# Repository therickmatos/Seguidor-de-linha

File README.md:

# Seguidor de linha — baseado no EVA-RT

Robotracer com ventoinha centrífuga para uma competição baseada no regulamento do TRIF 7ª edição.
Baseado no [EVA-RT](https://github.com/EXOTIC-TEAM-MX/EVA-RT) (© EXOTIC TEAM MX, AGPL-3.0).

- ATmega328P-AU, firmware EVA-RT 1.2.2 (mesmo mapa de pinos)
- 2× DRV8874 (motores coreless 1020), AO3400A na ventoinha
- Barra de 12× QRE1113 + 74HC4067, sensores de marca nos braços laterais
- LiPo 2S 350 mAh, contorno "B degraus" de 148,2 × 57,6 mm

## Estado
- [x] Componentes definidos
- [x] Contorno definitivo (`hardware/contorno/`)
- [x] Esquemático rev 1.0 em KiCad (`hardware/seguidor_base/seguidor_base.pdf`; fonte em `ferramentas/esquematico/`)
- [ ] Importação no EasyEDA Pro (em andamento; conferir com `hardware/seguidor_base/REDES.md`)
- [ ] Layout da placa (EasyEDA Pro)
- [ ] Pedido na JLC
- [ ] Montagem e firmware

## Estrutura
| Pasta | Conteúdo |
|---|---|
| `docs/` | decisões (as mais novas: `DECISOES_2026-11-04.md`), contorno e esquemático |
| `hardware/contorno/` | contorno B definitivo (DXF) e figuras de conferência |
| `hardware/seguidor_base/` | esquemático rev 1.0 (projeto KiCad, PDF), BOM, lista de redes (`REDES.md`) |
| `hardware/barra_v1/` | Gerber da barra de sensores V1 (12 sensores) |
| `hardware/figuras/` | posição do conector do Bluetooth |
| `Perseguidor de linha/` | perseguidor (placa sem os braços + receptor IR KY-022): projeto EasyEDA Pro e revisão |
| `ferramentas/esquematico/` | scripts que geram o esquemático KiCad, a BOM e a lista de redes |
| `referencias/eva-rt/` | cópia do EVA-RT: projeto EasyEDA Pro, Gerbers, PDFs, STL e firmware |

O seguidor em fenolite é outro projeto e não está neste repositório.

## Licença
GNU Affero General Public License v3.0 (`LICENSE`), a mesma do EVA-RT.

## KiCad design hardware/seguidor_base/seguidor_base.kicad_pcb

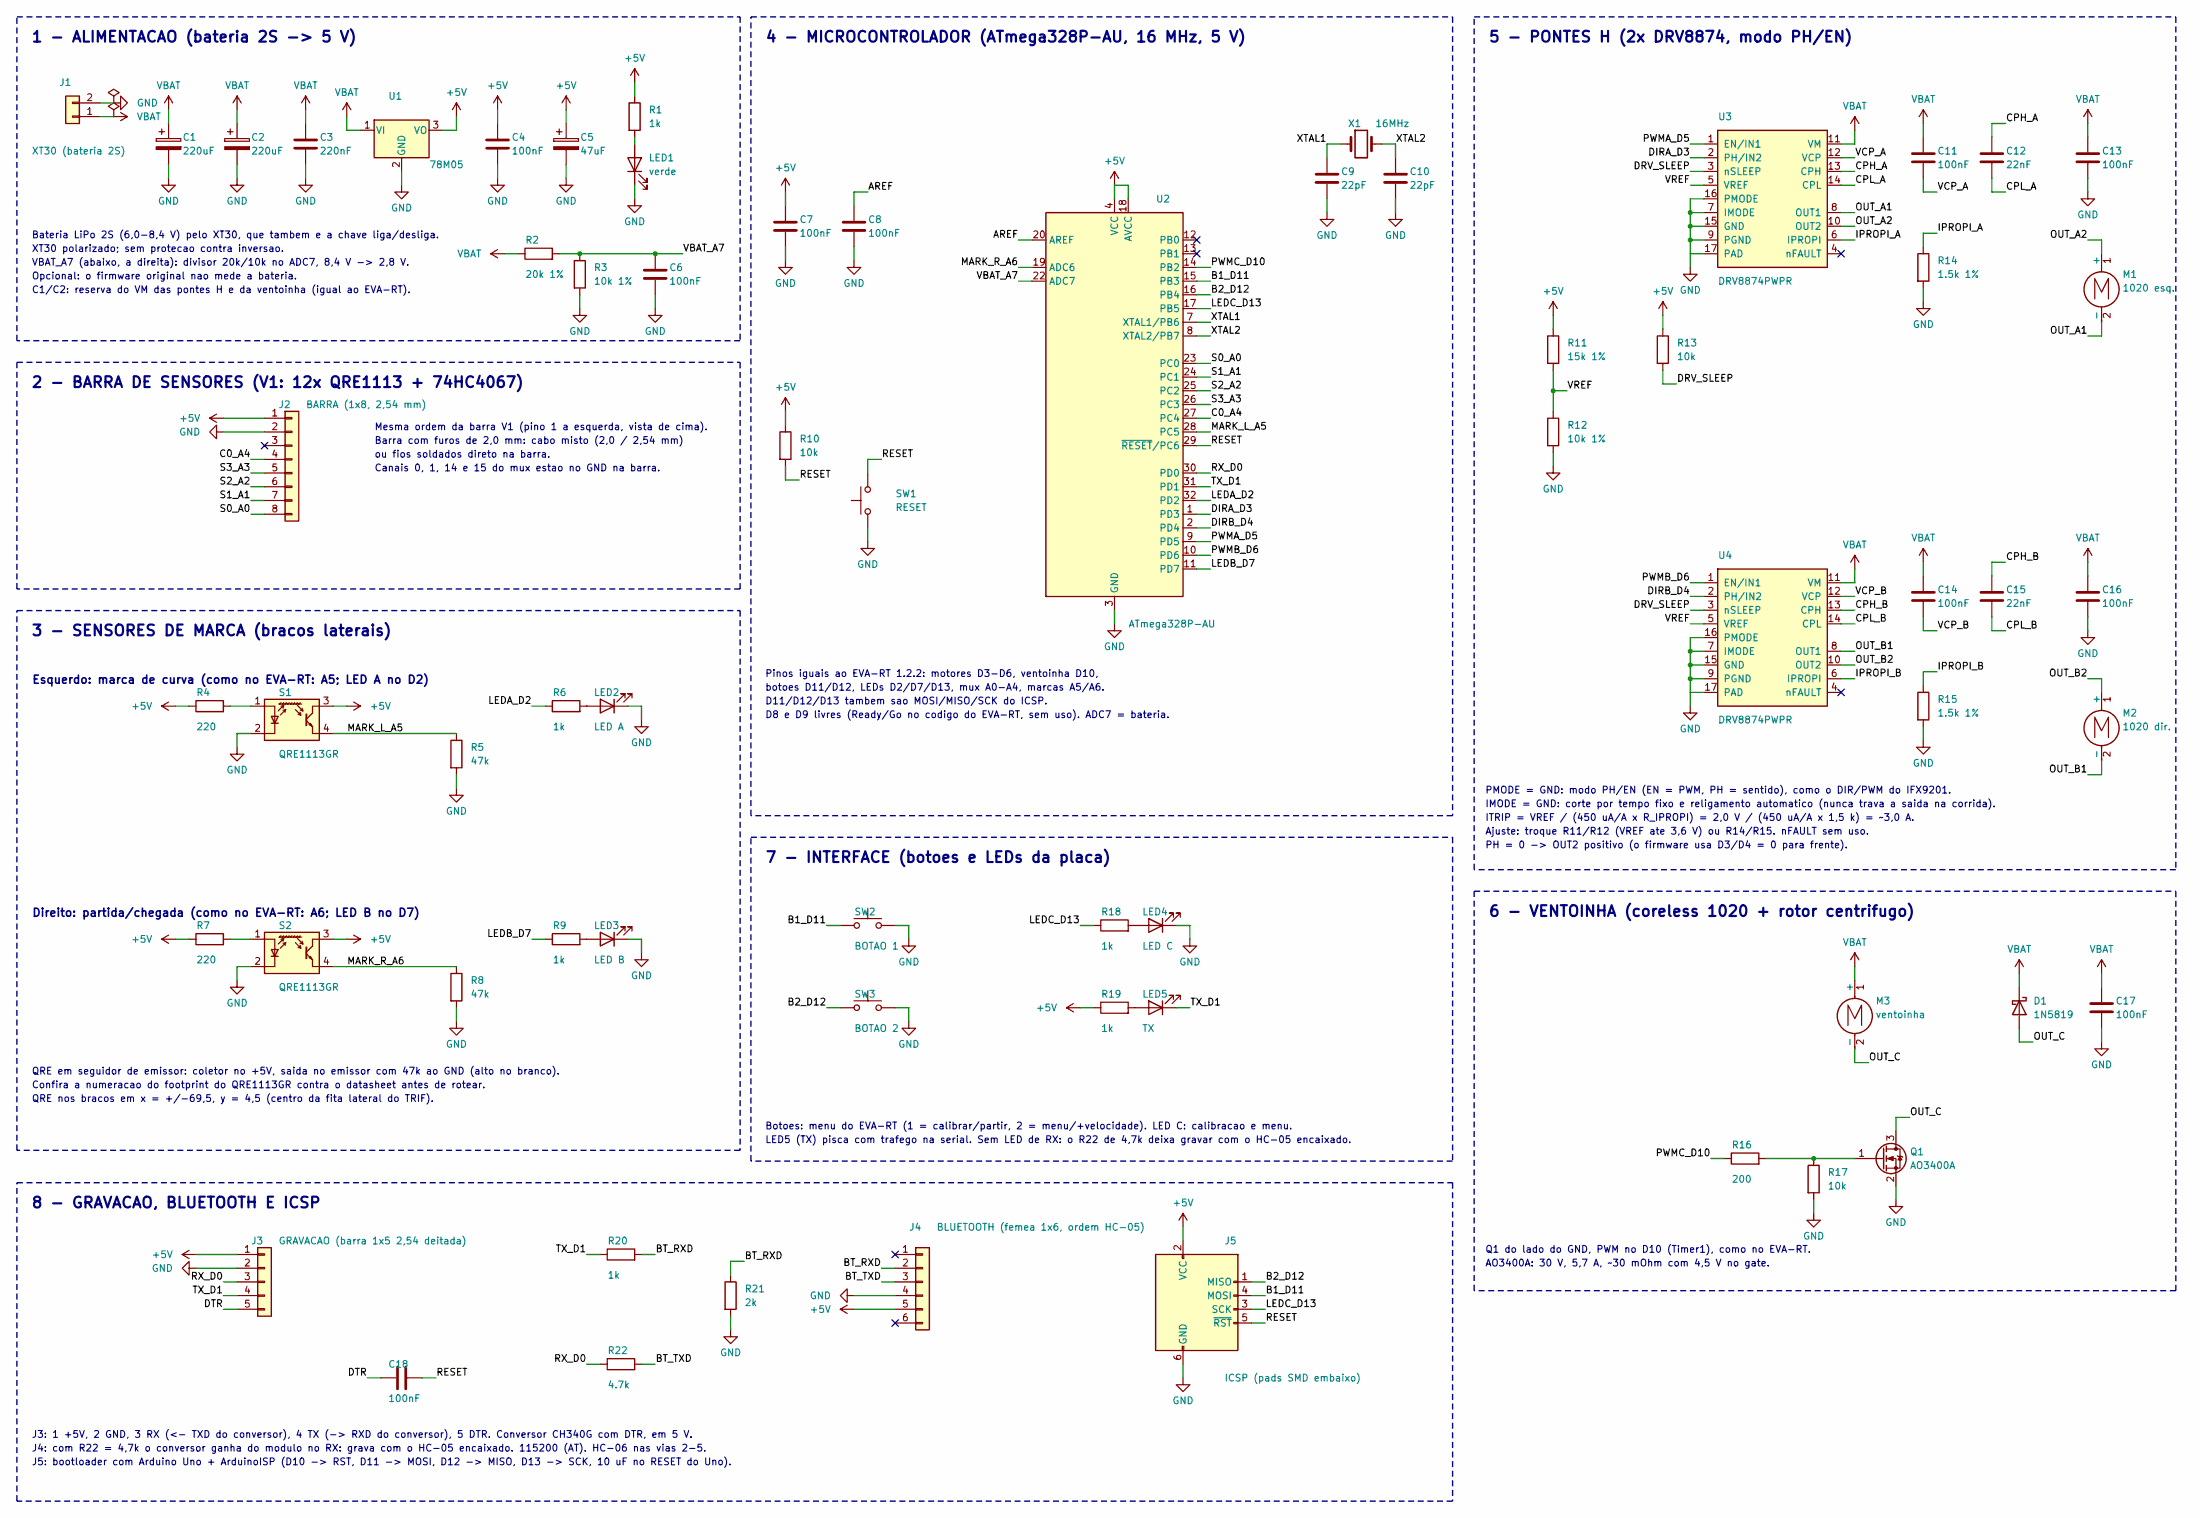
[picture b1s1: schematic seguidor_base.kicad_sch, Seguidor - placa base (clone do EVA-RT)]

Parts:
C1, C2: 220uF; C_RAD_D6.3_P2.5
C3: 220nF; C0603
C4, C6, C7, C8, C11, C13, C14, C16, C17, C18: 100nF; C0603
C5: 47uF; C1210
C9, C10: 22pF; C0603
C12, C15: 22nF; C0603
D1: 1N5819; SOD123
J1: XT30 (bateria 2S); XT30_VERTICAL_M_PROPOSTA; LCSC C99101
J2: BARRA (1x8, 2,54 mm); HDR_1x08_P2.54
J3: GRAVACAO (barra 1x5 2,54 deitada); HDR_1x05_P2.54_SMD_DEITADA
J4: BLUETOOTH (femea 1x6, ordem HC-05); HDR_F_1x06_P2.54
J5: ICSP (pads SMD embaixo); ICSP_6P_SMD_BOT
LED1: verde; LED0603
LED2: LED A; LED0603
LED3: LED B; LED0603
LED4: LED C; LED0603
LED5: TX; LED0603
M1: 1020 esq.; MOTOR_1020_2P
M2: 1020 dir.; MOTOR_1020_2P
M3: ventoinha; MOTOR_1020_2P
Q1: AO3400A; SOT23_AO3400A; LCSC C20917
R1, R6, R9, R18, R19, R20: 1k; R0603
R2: 20k 1%; R0603
R3, R12: 10k 1%; R0603
R4, R7: 220; R0603
R5, R8: 47k; R0603
R10, R13, R17: 10k; R0603
R11: 15k 1%; R0603
R14, R15: 1.5k 1%; R0603
R16: 200; R0603
R21: 2k; R0603
R22: 4.7k; R0603
S1, S2: QRE1113GR; QRE1113GR_SMD
SW1: RESET; SW_TACT_3x6_SMD_2P_RESET; LCSC C19271064
SW2: BOTAO 1; SW_TACT_3x6_SMD_2P; LCSC C19271064
SW3: BOTAO 2; SW_TACT_3x6_SMD_2P; LCSC C19271064
U1: 78M05; DPAK_TO252_3; LCSC C111265
U2: ATmega328P-AU; TQFP32_7x7_P0.8; LCSC C14877
U3, U4: DRV8874PWPR; HTSSOP16_PWP_DRV8874; LCSC C1855818
X1: 16MHz; XTAL_TXC_7A_5032_2P; LCSC C2450102

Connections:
+5V: C4.1, C5.1, C7.1, J2.1, J3.1, J4.5, J5.2 (VCC), R1.1, R4.1, R7.1, R10.1, R11.1, R13.1, R19.1, S1.3, S2.3, U1.3 (VO), U2.4 (VCC), U2.6 (VCC), U2.18 (AVCC)
AREF: C8.1, U2.20 (AREF)
B1_D11: J5.4 (MOSI), SW2.1, U2.15 (PB3)
B2_D12: J5.1 (MISO), SW3.1, U2.16 (PB4)
BT_RXD: J4.2, R20.2, R21.1
BT_TXD: J4.3, R22.2
C0_A4: J2.4, U2.27 (PC4)
CPH_A: C12.1, U3.13 (CPH)
CPH_B: C15.1, U4.13 (CPH)
CPL_A: C12.2, U3.14 (CPL)
CPL_B: C15.2, U4.14 (CPL)
DIRA_D3: U2.1 (PD3), U3.2 (PH/IN2)
DIRB_D4: U2.2 (PD4), U4.2 (PH/IN2)
DRV_SLEEP: R13.2, U3.3 (nSLEEP), U4.3 (nSLEEP)
DTR: C18.1, J3.5
GND: C1.2, C2.2, C3.2, C4.2, C5.2, C6.2, C7.2, C8.2, C9.2, C10.2, C13.2, C16.2, C17.2, J1.2, J2.2, J3.2, J4.4, J5.6 (GND), LED1.1 (K), LED2.1 (K), LED3.1 (K), LED4.1 (K), Q1.2 (S), R3.2, R5.2, R8.2, R12.2, R14.2, R15.2, R17.2, R21.2, S1.2 (K), S2.2 (K), SW1.1, SW2.2, SW3.2, U1.2 (GND), U2.3 (GND), U2.5 (GND), U2.21 (GND), U3.7 (IMODE), U3.9 (PGND), U3.15 (GND), U3.16 (PMODE), U3.17 (PAD), U4.7 (IMODE), U4.9 (PGND), U4.15 (GND), U4.16 (PMODE), U4.17 (PAD)
IPROPI_A: R14.1, U3.6 (IPROPI)
IPROPI_B: R15.1, U4.6 (IPROPI)
LEDA_D2: R6.1, U2.32 (PD2)
LEDB_D7: R9.1, U2.11 (PD7)
LEDC_D13: J5.3 (SCK), R18.1, U2.17 (PB5)
MARK_L_A5: R5.1, S1.4, U2.28 (PC5)
MARK_R_A6: R8.1, S2.4, U2.19 (ADC6)
unnamed: LED1.2 (A), R1.2
unnamed: LED2.2 (A), R6.2
unnamed: LED3.2 (A), R9.2
unnamed: LED4.2 (A), R18.2
unnamed: LED5.2 (A), R19.2
unnamed: Q1.1 (G), R16.2, R17.1
unnamed: R4.2, S1.1 (A)
unnamed: R7.2, S2.1 (A)
OUT_A1: M1.2 (-), U3.8 (OUT1)
OUT_A2: M1.1 (+), U3.10 (OUT2)
OUT_B1: M2.2 (-), U4.8 (OUT1)
OUT_B2: M2.1 (+), U4.10 (OUT2)
OUT_C: D1.2 (A), M3.2 (-), Q1.3 (D)
PWMA_D5: U2.9 (PD5), U3.1 (EN/IN1)
PWMB_D6: U2.10 (PD6), U4.1 (EN/IN1)
PWMC_D10: R16.1, U2.14 (PB2)
RESET: C18.2, J5.5 (~RST), R10.2, SW1.2, U2.29 (~RESET/PC6)
RX_D0: J3.3, R22.1, U2.30 (PD0)
S0_A0: J2.8, U2.23 (PC0)
S1_A1: J2.7, U2.24 (PC1)
S2_A2: J2.6, U2.25 (PC2)
S3_A3: J2.5, U2.26 (PC3)
TX_D1: J3.4, LED5.1 (K), R20.1, U2.31 (PD1)
VBAT: C1.1, C2.1, C3.1, C11.1, C13.1, C14.1, C16.1, C17.1, D1.1 (K), J1.1, M3.1 (+), R2.1, U1.1 (VI), U3.11 (VM), U4.11 (VM)
VBAT_A7: C6.1, R2.2, R3.1, U2.22 (ADC7)
VCP_A: C11.2, U3.12 (VCP)
VCP_B: C14.2, U4.12 (VCP)
VREF: R11.2, R12.1, U3.5 (VREF), U4.5 (VREF)
XTAL1: C9.1, U2.7 (XTAL1/PB6), X1.1
XTAL2: C10.1, U2.8 (XTAL2/PB7), X1.2

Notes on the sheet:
1 - ALIMENTACAO (bateria 2S -> 5 V)
Bateria LiPo 2S (6,0-8,4 V) pelo XT30, que tambem e a chave liga/desliga.
XT30 polarizado; sem protecao contra inversao.
VBAT_A7 (abaixo, a direita): divisor 20k/10k no ADC7, 8,4 V -> 2,8 V.
Opcional: o firmware original nao mede a bateria.
C1/C2: reserva do VM das pontes H e da ventoinha (igual ao EVA-RT).
2 - BARRA DE SENSORES (V1: 12x QRE1113 + 74HC4067)
Mesma ordem da barra V1 (pino 1 a esquerda, vista de cima).
Barra com furos de 2,0 mm: cabo misto (2,0 / 2,54 mm)
ou fios soldados direto na barra.
Canais 0, 1, 14 e 15 do mux estao no GND na barra.
3 - SENSORES DE MARCA (bracos laterais)
Esquerdo: marca de curva (como no EVA-RT: A5; LED A no D2)
Direito: partida/chegada (como no EVA-RT: A6; LED B no D7)
QRE em seguidor de emissor: coletor no +5V, saida no emissor com 47k ao GND (alto no branco).
Confira a numeracao do footprint do QRE1113GR contra o datasheet antes de rotear.
QRE nos bracos em x = +/-69,5, y = 4,5 (centro da fita lateral do TRIF).
4 - MICROCONTROLADOR (ATmega328P-AU, 16 MHz, 5 V)
Pinos iguais ao EVA-RT 1.2.2: motores D3-D6, ventoinha D10,
botoes D11/D12, LEDs D2/D7/D13, mux A0-A4, marcas A5/A6.
D11/D12/D13 tambem sao MOSI/MISO/SCK do ICSP.
D8 e D9 livres (Ready/Go no codigo do EVA-RT, sem uso). ADC7 = bateria.
5 - PONTES H (2x DRV8874, modo PH/EN)
PMODE = GND: modo PH/EN (EN = PWM, PH = sentido), como o DIR/PWM do IFX9201.
IMODE = GND: corte por tempo fixo e religamento automatico (nunca trava a saida na corrida).
ITRIP = VREF / (450 uA/A x R_IPROPI) = 2,0 V / (450 uA/A x 1,5 k) = ~3,0 A.
Ajuste: troque R11/R12 (VREF ate 3,6 V) ou R14/R15. nFAULT sem uso.
PH = 0 -> OUT2 positivo (o firmware usa D3/D4 = 0 para frente).
6 - VENTOINHA (coreless 1020 + rotor centrifugo)
Q1 do lado do GND, PWM no D10 (Timer1), como no EVA-RT.
AO3400A: 30 V, 5,7 A, ~30 mOhm com 4,5 V no gate.
7 - INTERFACE (botoes e LEDs da placa)
Botoes: menu do EVA-RT (1 = calibrar/partir, 2 = menu/+velocidade). LED C: calibracao e menu.
LED5 (TX) pisca com trafego na serial. Sem LED de RX: o R22 de 4,7k deixa gravar com o HC-05 encaixado.
8 - GRAVACAO, BLUETOOTH E ICSP
J3: 1 +5V, 2 GND, 3 RX (<- TXD do conversor), 4 TX (-> RXD do conversor), 5 DTR. Conversor CH340G com DTR, em 5 V.
J4: com R22 = 4,7k o conversor ganha do modulo no RX: grava com o HC-05 encaixado. 115200 (AT). HC-06 nas vias 2-5.
J5: bootloader com Arduino Uno + ArduinoISP (D10 -> RST, D11 -> MOSI, D12 -> MISO, D13 -> SCK, 10 uF no RESET do Uno).

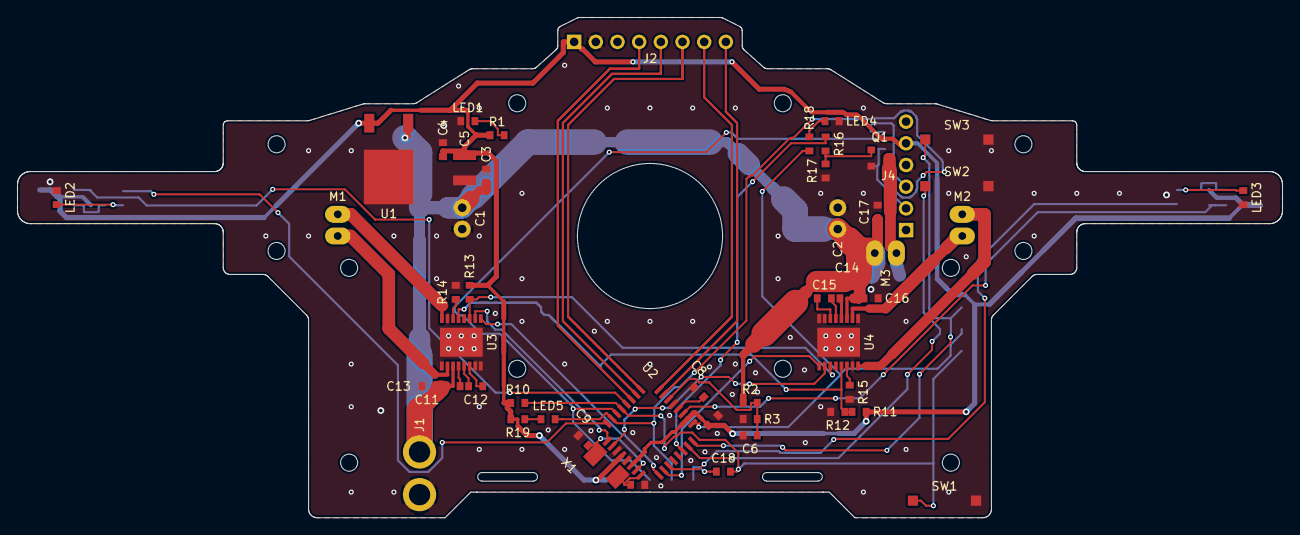
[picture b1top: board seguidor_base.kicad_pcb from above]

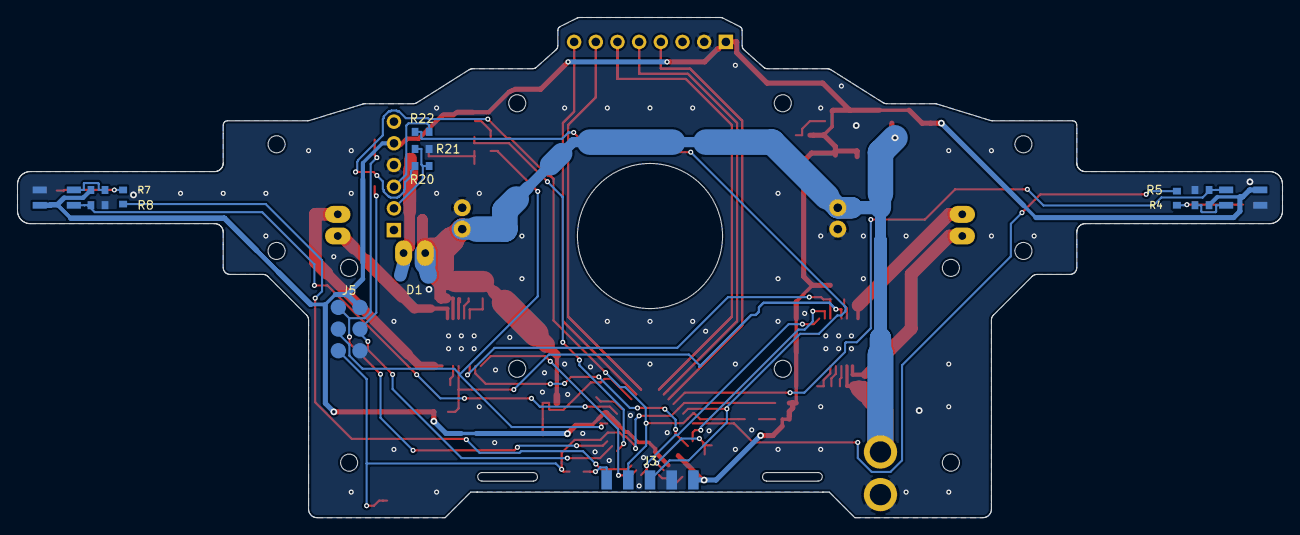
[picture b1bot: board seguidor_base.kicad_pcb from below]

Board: 2 copper layers, 148.2 x 58.6 mm, 65 parts (14 on the bottom side), 53 nets.

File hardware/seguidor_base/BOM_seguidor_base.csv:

Qtd;Referencias;Valor;Encapsulamento;LCSC;Montagem;EVA-RT;Observacao
2;C1 C2;220uF;eletrolitico 25 V, radial D6,3 mm P2,5;;sim;igual;entre os pes da carcaca, como no EVA-RT
1;C3;220nF;0603 50 V;;sim;igual;
4;C4 C7 C8 C18;100nF;0603;;sim;"igual; novo";"junto aos pinos VCC; AREF (referencia = AVCC no firmware); reset automatico pelo DTR"
1;C5;47uF;ceramico X5R >= 10 V, 1210;;sim;igual;"07/11: 1210 (achado pelo Erick); o tantalo 3216 do EVA-RT tambem serve com footprint 3216"
2;C9 C10;22pF;0603;;sim;novo;
2;C11 C14;100nF;0603 16 V X7R;;sim;novo;VCP -> VM
2;C12 C15;22nF;0603 50 V X7R;;sim;novo;CPH -> CPL (tensao >= VM)
2;C13 C16;100nF;0603 25 V X7R;;sim;igual;VM, junto ao pino 11
1;C17;100nF;0603 25 V;;sim;igual;
1;D1;1N5819;SOD-123 (B5819W) ou 1N5819 nos terminais do motor;;sim;novo;"diodo de roda livre (novo; o EVA-RT nao tem)"
1;J1;XT30 (bateria 2S);"XT30U-M (macho de cabo; copos soldados nos furos, em pe)";C99101;sim;VIN;"pino 1 = + (lado reto), pino 2 = -; em pe por dentro do suporte esq.; medir os copos e cortar rente embaixo; versao de placa: XT30UPB-M (C428721)"
1;J2;BARRA (1x8, 2,54 mm);barra de pinos 1x8 2,54 mm;;sim;FPC1 (FPC 10 vias);
1;J3;GRAVACAO (barra 1x5 2,54 deitada);5 pads SMD 1,25 x 2,25 + barra macho 1x5 2,54 deitada;;sim;Converter Conn Master;borda traseira, face de baixo (como o EVA-RT)
1;J4;BLUETOOTH (femea 1x6, ordem HC-05);barra femea 1x6 2,54 mm;;sim;novo;"frente direita, x = 32,5; HC-06 nas vias 2-5 (virado)"
1;J5;ICSP (pads SMD embaixo);6 pads SMD D1,8 em grade 2,54;;sim;USB to ASP Conn Master;"posicoes do EVA-RT: x 33,97/36,51; y -8,36/-10,90/-13,44"
1;LED1;verde;0603;;sim;igual;indica 5 V presente
1;LED2;LED A;0603;;sim;igual;
1;LED3;LED B;0603;;sim;igual;
1;LED4;LED C;0603;;sim;igual;"vermelho; o LED em paralelo do EVA-RT foi retirado"
1;LED5;TX;0603;;sim;igual;
1;M1;1020 esq.;2 pads;;sim;igual;"coreless 1020 7,4 V; se girar ao contrario, inverta os fios"
1;M2;1020 dir.;2 pads;;sim;igual;"coreless 1020 7,4 V; se girar ao contrario, inverta os fios"
1;M3;ventoinha;2 pads;;sim;igual;coreless 1020 7,4 V
1;Q1;AO3400A;SOT-23 (1 = G, 2 = S, 3 = D);C20917;sim;Q1 (outro MOSFET);"no lugar do IRFR3411/RM10N100LD; liga totalmente com 5 V no gate"
6;R1 R6 R9 R18 R19 R20;1k;0603;;sim;"igual; novo";divisor 5 V -> 3,3 V
2;R4 R7;220;0603;;sim;igual;
2;R5 R8;47k;0603;;sim;igual;
3;R10 R13 R17;10k;0603;;sim;"R3 (1k); novo; igual";"EVA-RT usava 1k; 10k com reset automatico por DTR; nSLEEP sempre alto (pull-down interno de 100k); gate -> GND (desligado no boot)"
1;R11;15k 1%;0603;;sim;novo;VREF = 2,0 V
1;R12;10k 1%;0603;;sim;novo;VREF = 2,0 V
2;R14 R15;1.5k 1%;0603;;sim;novo;IPROPI -> limite de corrente
1;R16;200;0603;;sim;igual;gate
1;R21;2k;0603;;sim;novo;divisor 5 V -> 3,3 V
1;R22;4.7k;0603;;sim;novo;4,7k: grava com o HC-05 encaixado (sem LED de RX)
2;S1 S2;QRE1113GR;SMD 4 pinos;;sim;igual;datasheet: 1 = anodo, 2 = catodo, 3 = coletor, 4 = emissor
1;SW1;RESET;chave tactil SMD 3,7 x 6,1, 2 terminais (Jianfu TVBM17-025CF-R);C19271064;sim;igual;"terminais com 8,0 de ponta a ponta; pads encurtados (8,6 no total) para caber ao lado do J4"
1;SW2;BOTAO 1;chave tactil SMD 3,7 x 6,1, 2 terminais (Jianfu TVBM17-025CF-R);C19271064;sim;igual;"terminais com 8,0 de ponta a ponta; pads encurtados (8,6 no total) para caber ao lado do J4"
1;SW3;BOTAO 2;chave tactil SMD 3,7 x 6,1, 2 terminais (Jianfu TVBM17-025CF-R);C19271064;sim;igual;"terminais com 8,0 de ponta a ponta; pads encurtados (8,6 no total) para caber ao lado do J4"
1;U1;78M05;TO-252 (DPAK);C111265;sim;igual;
1;U2;ATmega328P-AU;TQFP-32;C14877;sim;igual;do Nano/Uno doador (com bootloader) ou novo + bootloader pelo ICSP
2;U3 U4;DRV8874PWPR;HTSSOP-16 (PWP), pad termico com vias;C1855818;sim;"IFX_A1 (IFX9201); IFX_B1 (IFX9201)";"esq.; dir."
1;X1;16MHz;cristal SMD 5032 de 2 pads (TXC 7A-16.000MAAJ-T);C2450102;sim;X1 (ressonador 3 pinos);16 MHz, CL 18 pF, ESR 50 ohm, +-30 ppm, 1,2 mm de altura (fica sob a bateria)
1;C6;100nF;0603;;opcional (bateria);novo;filtro da medicao (opcional)
1;R2;20k 1%;0603;;opcional (bateria);novo;medicao da bateria (opcional)
1;R3;10k 1%;0603;;opcional (bateria);novo;medicao da bateria (opcional)

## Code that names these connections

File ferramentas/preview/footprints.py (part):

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    [_pad("1", -4.25, 0, 4.5, 2.0), _pad("2", 4.25, 0, 4.5, 2.0)],
    (11.4, 4.7), 3.5, False,
    "Cristal HC-49/S SMD 2 terminais (X1 16 MHz, alternativa do BOM). KiCad "
    "Crystal_SMD_HC49-SD: pads 4,5 x 2,0 em +-4,25; corpo 11,4 x 4,7 (F.Fab). Pino 1 = XTAL1, "
    "pino 2 = XTAL2 (sem pinos de GND). Altura 3,5 estimada. Default de X1: por ser o maior, "
    "serve de caso conservador para colisao.")

# 07/11: cristal TXC 7A-16.000MAAJ-T (16 MHz, CL 18 pF, ESR 50, +-30 ppm; LCSC C2450102), 5,0 x 3,2 x 1,2,
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    "-1,50 e -4,04 (centro em y = -2,77, dado por corpo_xy); distancia furo -> face do corpo = "
    "1,50 mm; pontas dos pinos dobrados ate y = -10,04 (6,0 mm alem do corpo, altura ~2,5 mm). "
    "Pino 1 (+5V) em x = +5,08 (ordem invertida em relacao ao J2, por causa da rotacao "
    "fisica). Pinos 1..5 = +5V, GND, RX, TX, DTR. Cortesia calculada sem as pontas.",
    corpo_xy=(0.0, -2.77))

_pads_f6 = []
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

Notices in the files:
ferramentas/preview/footprints.py:
Clone do EVA-RT (EXOTIC TEAM MX, AGPL-3.0). Este modulo so descreve geometria
hardware/seguidor_base/kicad/seguidor_base.kicad_sch:
Baseado no EVA-RT (c) EXOTIC TEAM MX, AGPL-3.0
